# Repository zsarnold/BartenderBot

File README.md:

# BartenderBot
This respository houses all of the code and cad files for the BartenderBot. The idea behind this machine is to automate the creation of an mixed drink. The machine should create the same drink every single time with the same ratios.

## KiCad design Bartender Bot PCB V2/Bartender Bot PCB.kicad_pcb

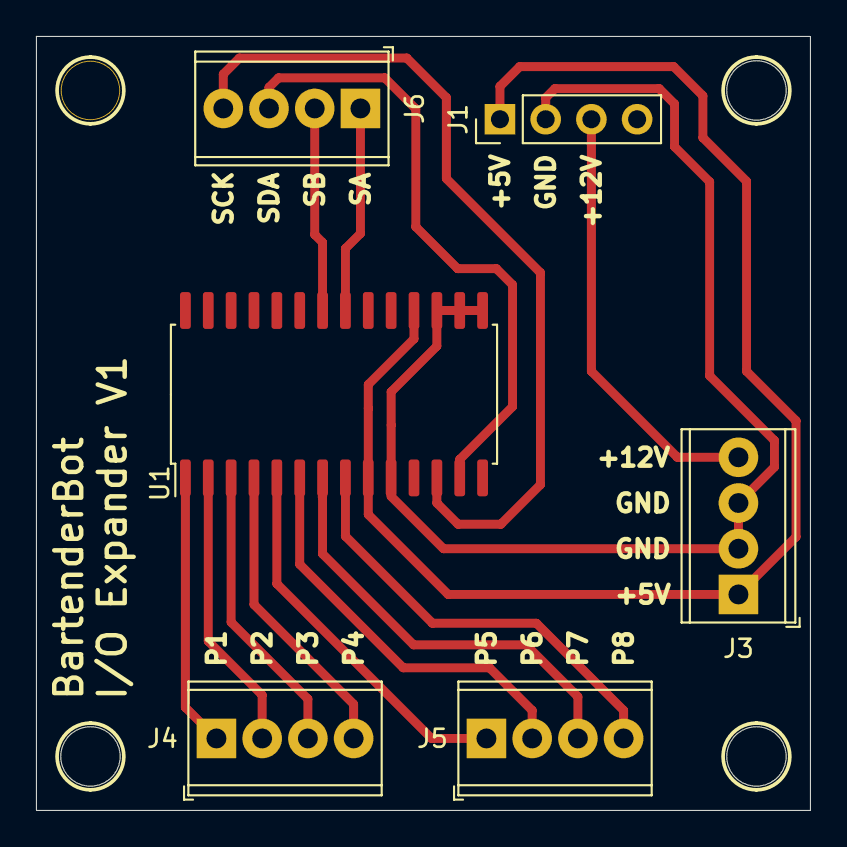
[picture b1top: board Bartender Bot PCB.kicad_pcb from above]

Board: 2 copper layers, 43.0 x 43.0 mm, 6 parts (0 on the bottom side), 15 nets.

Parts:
J1: Conn_01x04; PinHeader_1x04_P2.54mm_Vertical
J3, J4, J5, J6: Screw_Terminal_01x04; TerminalBlock_Phoenix_MPT-0,5-4-2.54_1x04_P2.54mm_Horizontal
U1: MCP23017_SO; SOIC-28W_7.5x17.9mm_P1.27mm

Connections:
+5V: J1.1, J3.1, U1.9, U1.18
+12V: J1.3, J3.4
/Pump1: J4.1, U1.1
/Pump2: J4.2, U1.2
/Pump3: J4.3, U1.3
/Pump4: J4.4, U1.4
/Pump5: J5.1, U1.5
/Pump6: J5.2, U1.6
/Pump7: J5.3, U1.7
/Pump8: J5.4, U1.8
/SCK: J6.4, U1.12
/SDA: J6.3, U1.13
/StepA: J6.1, U1.21
/StepB: J6.2, U1.22
GND: J1.2, J3.2, J3.3, U1.10, U1.15, U1.16, U1.17

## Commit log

2020-11-18 First push. Pseudo code started.
2020-11-18 more psuedocode for pump,covey,step
2020-11-18 links
2020-11-19 notes
2020-11-19 cad update
2020-11-29 new STLs
2020-11-29 motor mount
2020-12-04 PCB Final
2020-12-26 New pcb version
2020-12-29 i2c adr info
2020-12-29 Reorganization, initialization program
2020-12-29 Base UI python script
2020-12-29 Reorganization part 2
2020-12-29 Screen Program Changes
2020-12-31 pump
2020-12-31 Drink
2021-01-04 Added drinkDictionary to build master drink list
2021-01-04 Home screen and home button functionality
2021-01-04 Setup modular tiles dependant on dictionary size
